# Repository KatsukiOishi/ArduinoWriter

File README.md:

# ArduinoWriter
Arduinoボードのブート焼き入れから、シリアル書き込みまで対応させるボード

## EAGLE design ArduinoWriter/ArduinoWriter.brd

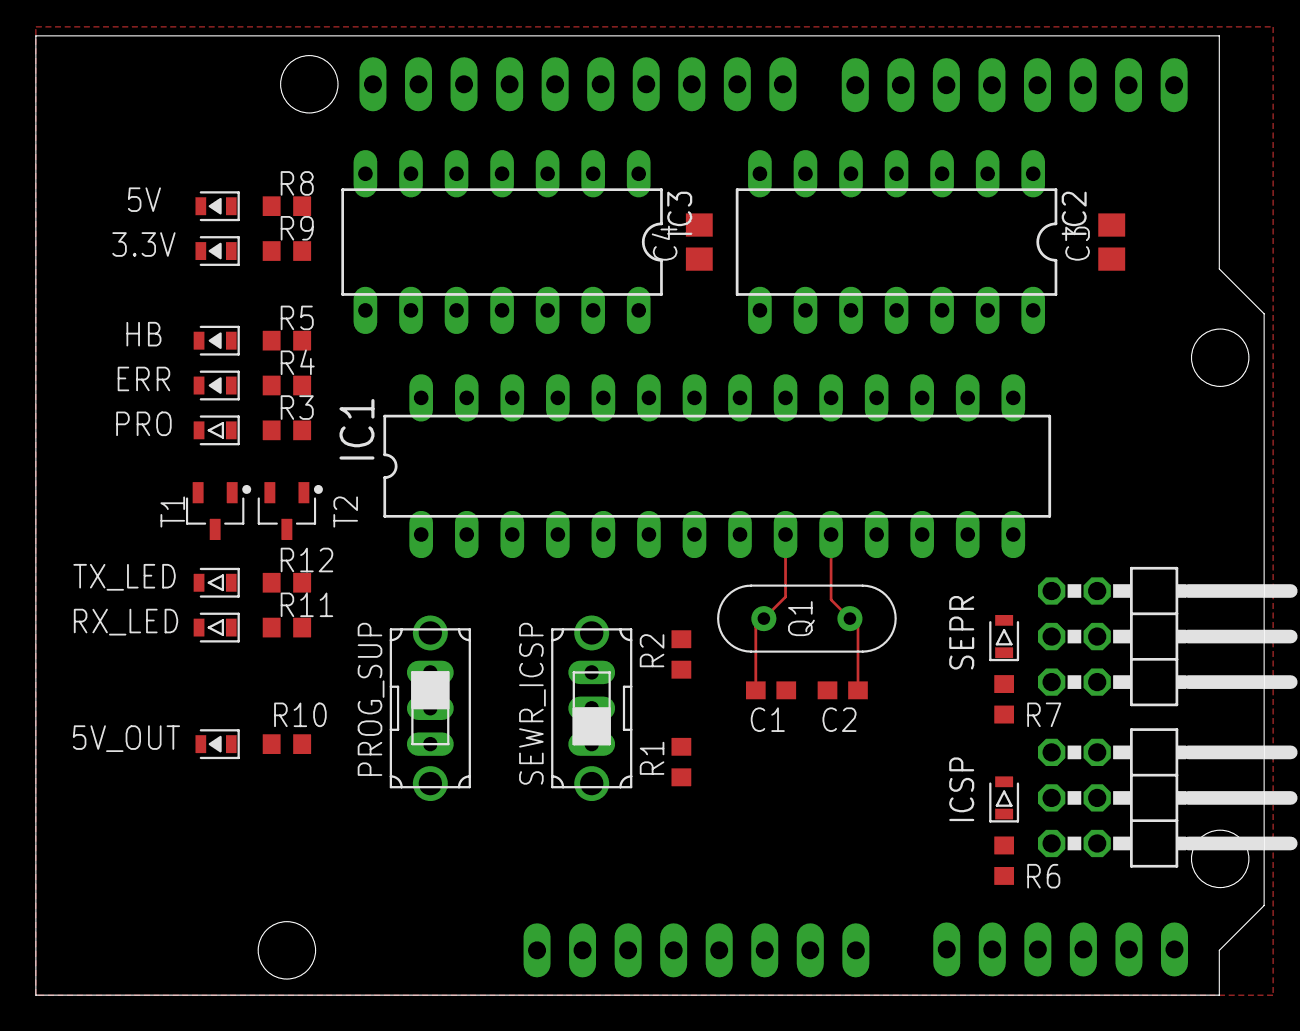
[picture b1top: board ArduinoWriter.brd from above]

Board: 2 copper layers, 68.5 x 53.5 mm, 37 parts (0 on the bottom side), 38 nets.

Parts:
3.3V, 5V, 5V_OUT: OSBL1608C1A; LEDC1608X39N_B
C1, C2: 22p; C0603
C3, C4: 10u; C0805
ERR: OSHR1608C1A; LEDC1608X39N_R
HB: OSHR1608C1A; LEDC1608X39N_R
IC1: ATMEGA328-PU; DIL28-3
IC2: TC74HC08AP; DIL14
IC3: TC74HC32AP; DIL14
ICSP: 2X03/90
ISPMODE: OSTG1608C1A; LEDC1608X39N_G
PRO: OSTG1608C1A; LEDC1608X39N_G
PROG_SUP: SS-12D01-VG4
Q1: HUSG-16.000-20; XTALRR480W50L990T368H350B
R1, R2: 10k; R0603
R3, R4, R5, R6, R7, R8, R9, R10, R11, R12: 1k; R0603
RX_LED: OSTG1608C1A; LEDC1608X39N_G
SEPR: 2X03/90
SEWRMODE: OSTG1608C1A; LEDC1608X39N_G
SEWR_ICSP: SS-12D01-VG4
T1, T2: IRLML6344TRPBF; SOT95P240X110-3N
TX_LED: OSTG1608C1A; LEDC1608X39N_G
U1: ARRDUINOUNO-NOSILK; ARDUINOUNO_NOSILK

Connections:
+3.3V: R9.2, U1.3.3V
+5V: C3.1, C4.1, IC1.7, IC1.20, IC2.14, IC3.14, PROG_SUP.COM, R8.2, R11.2, R12.2, SEWR_ICSP.COM, U1.5V
ERROR: IC1.14, R4.2
GND: 3.3V.2, 5V.2, 5V_OUT.2, C1.1, C2.1, C3.2, C4.2, ERR.2, HB.2, IC1.8, IC1.22, IC2.7, IC3.7, IC3.10, IC3.13, ICSP.6, ISPMODE.K, PRO.K, R1.1, R2.1, SEPR.6, SEWRMODE.K, T1.2, T2.2, U1.GND, U1.GND1, U1.GND2
HEARTBEAT: IC1.15, R5.2
ICSP_RESET: IC1.16, ICSP.5
MISO: IC1.18, ICSP.1
MOSI: IC1.17, ICSP.4
unnamed: C2.2, IC1.10, Q1.1
unnamed: C1.2, IC1.9, Q1.2
unnamed: PRO.A, R3.1
unnamed: ERR.1, R4.1
unnamed: HB.1, R5.1
unnamed: ISPMODE.A, R6.1
unnamed: R7.1, SEWRMODE.A
unnamed: 5V.1, R8.1
unnamed: 3.3V.1, R9.1
unnamed: 5V_OUT.1, R10.1
unnamed: RX_LED.K, T1.3
unnamed: T2.3, TX_LED.K
unnamed: R11.1, RX_LED.A
unnamed: R12.1, TX_LED.A
PCRX_ICTX: IC2.2, IC2.5, T1.1, U1.1
PCTX_ICRX: IC2.10, IC2.13, T2.1, U1.0
PROGRAMMING: IC1.13, R3.2
PROG_SUPPLY: ICSP.2, PROG_SUP.NO, R10.2, SEPR.2
RESET_SIG: IC3.2, IC3.5, U1.RESET
SCK: IC1.19, ICSP.3
SE_RESET: IC3.3, SEPR.5
SE_RX: IC2.11, SEPR.1
SE_SW: IC2.4, IC2.12, IC3.4, IC3.9, R1.2, SEWR_ICSP.NC
SE_SW_LED: IC3.8, R7.2
SE_TX: IC2.6, SEPR.3
WRITER_RESET: IC1.1, IC3.6
WRITER_RX: IC1.2, IC2.8
WRITER_TX: IC1.3, IC2.3
WR_SW: IC2.1, IC2.9, IC3.1, IC3.12, R2.2, SEWR_ICSP.NO
WR_SW_LED: IC3.11, R6.2

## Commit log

2022-01-30 .gitignore記述
2022-01-30 Eagleプロジェクト立ち上げ
2022-01-30 回路図面制作途中
2022-01-30 SEWR_ICSP 切替回路実装
2022-01-31 レイアウト完了
2022-02-01 配線・シルク完
2022-02-04 RXTX欠陥部修正
2022-02-05 スイッチ・一部表示変更
2022-02-05 CAM完了
